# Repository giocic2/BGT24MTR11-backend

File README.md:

# BGT24MTR11-backend
KiCAD project of low frequency amplification and filtering stage

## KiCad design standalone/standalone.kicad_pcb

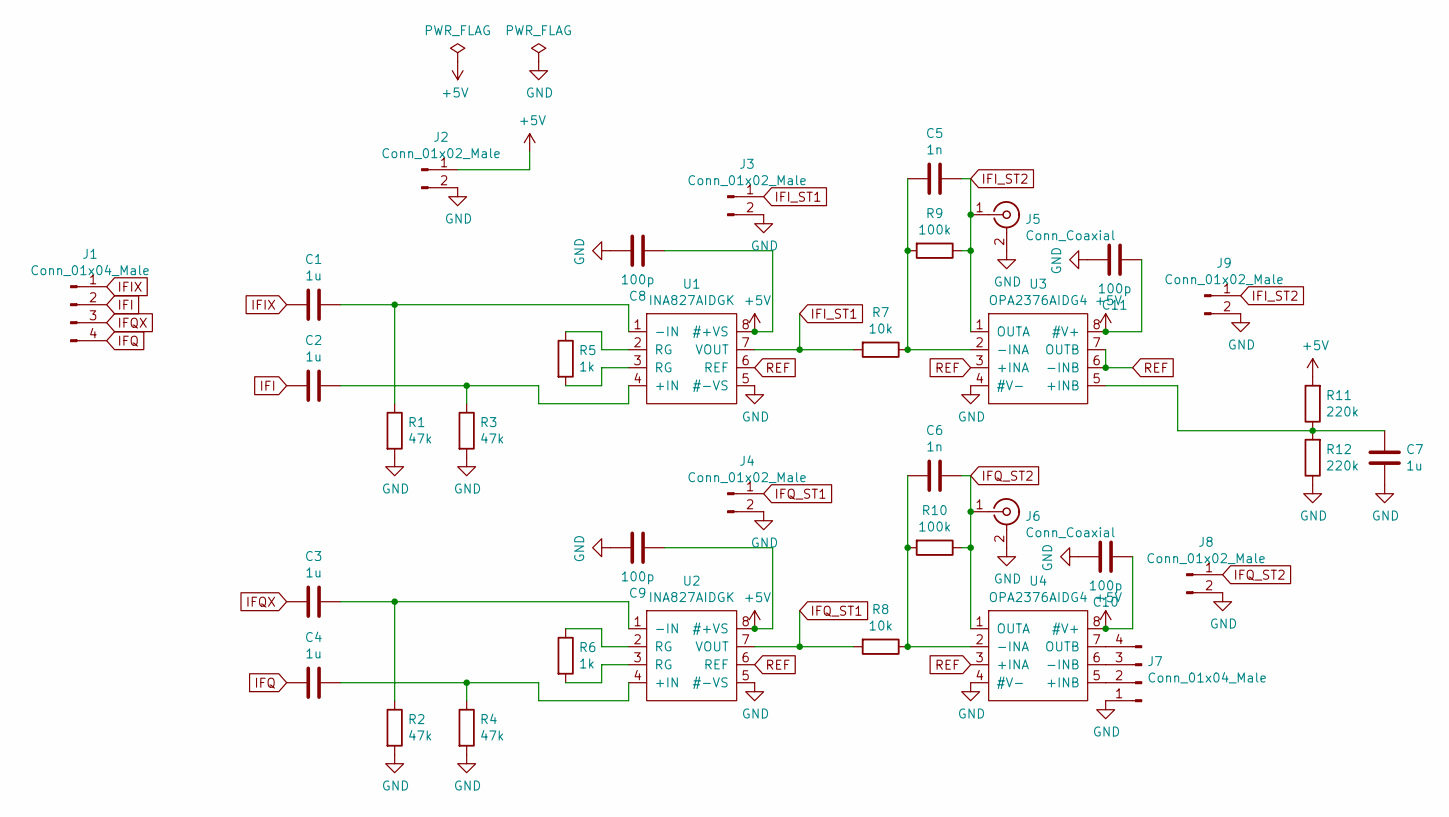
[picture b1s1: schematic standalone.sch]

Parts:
C1, C2, C3, C4, C7: 1u; C_0603_1608Metric_Pad1.08x0.95mm_HandSolder
C5, C6: 1n; C_0603_1608Metric_Pad1.08x0.95mm_HandSolder
C8, C9, C10, C11: 100p; C_0603_1608Metric_Pad1.08x0.95mm_HandSolder
J1, J7: Conn_01x04_Male; PinHeader_1x04_P2.54mm_Vertical
J2, J3, J4, J8, J9: Conn_01x02_Male; PinHeader_1x02_P2.54mm_Vertical
J5, J6: Conn_Coaxial; BNC_Amphenol_B6252HB-NPP3G-50_Horizontal
R1, R2, R3, R4: 47k; R_0603_1608Metric_Pad0.98x0.95mm_HandSolder
R5, R6: 1k; R_0603_1608Metric_Pad0.98x0.95mm_HandSolder
R7, R8: 10k; R_0603_1608Metric_Pad0.98x0.95mm_HandSolder
R9, R10: 100k; R_0603_1608Metric_Pad0.98x0.95mm_HandSolder
R11, R12: 220k; R_0603_1608Metric_Pad0.98x0.95mm_HandSolder
U1, U2: INA827AIDGK; VSSOP-8_3.0x3.0mm_P0.65mm
U3, U4: OPA2376AIDG4; SOIC-8_3.9x4.9mm_P1.27mm

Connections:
+5V: C8.2, C9.2, C10.2, C11.2, J2.1, R11.2, U1.8 (#+VS), U2.8 (#+VS), U3.8 (#V+), U4.8 (#V+)
GND: C7.1, C8.1, C9.1, C10.1, C11.1, J2.2, J3.2, J4.2, J5.2 (Ext), J6.2 (Ext), J7.1, J8.2, J9.2, R1.2, R2.2, R3.2, R4.2, R12.1, U1.5 (#-VS), U2.5 (#-VS), U3.4 (#V-), U4.4 (#V-)
IFI: C2.2, J1.2
IFIX: C1.2, J1.1
IFI_ST1: J3.1, R7.2, U1.7 (VOUT)
IFI_ST2: C5.1, J5.1 (In), J9.1, R9.1, U3.1 (OUTA)
IFQ: C4.2, J1.4
IFQX: C3.2, J1.3
IFQ_ST1: J4.1, R8.2, U2.7 (VOUT)
IFQ_ST2: C6.1, J6.1 (In), J8.1, R10.1, U4.1 (OUTA)
unnamed: C1.1, R1.1, U1.1 (-IN)
unnamed: C2.1, R3.1, U1.4 (+IN)
unnamed: C3.1, R2.1, U2.1 (-IN)
unnamed: C4.1, R4.1, U2.4 (+IN)
unnamed: C5.2, R7.1, R9.2, U3.2 (-INA)
unnamed: C6.2, R8.1, R10.2, U4.2 (-INA)
unnamed: C7.2, R11.1, R12.2, U3.5 (+INB)
unnamed: J7.2, U4.5 (+INB)
unnamed: J7.3, U4.6 (-INB)
unnamed: J7.4, U4.7 (OUTB)
unnamed: R5.1, U1.2 (RG)
unnamed: R5.2, U1.3 (RG)
unnamed: R6.1, U2.2 (RG)
unnamed: R6.2, U2.3 (RG)
REF: U1.6 (REF), U2.6 (REF), U3.3 (+INA), U3.6 (-INB), U3.7 (OUTB), U4.3 (+INA)

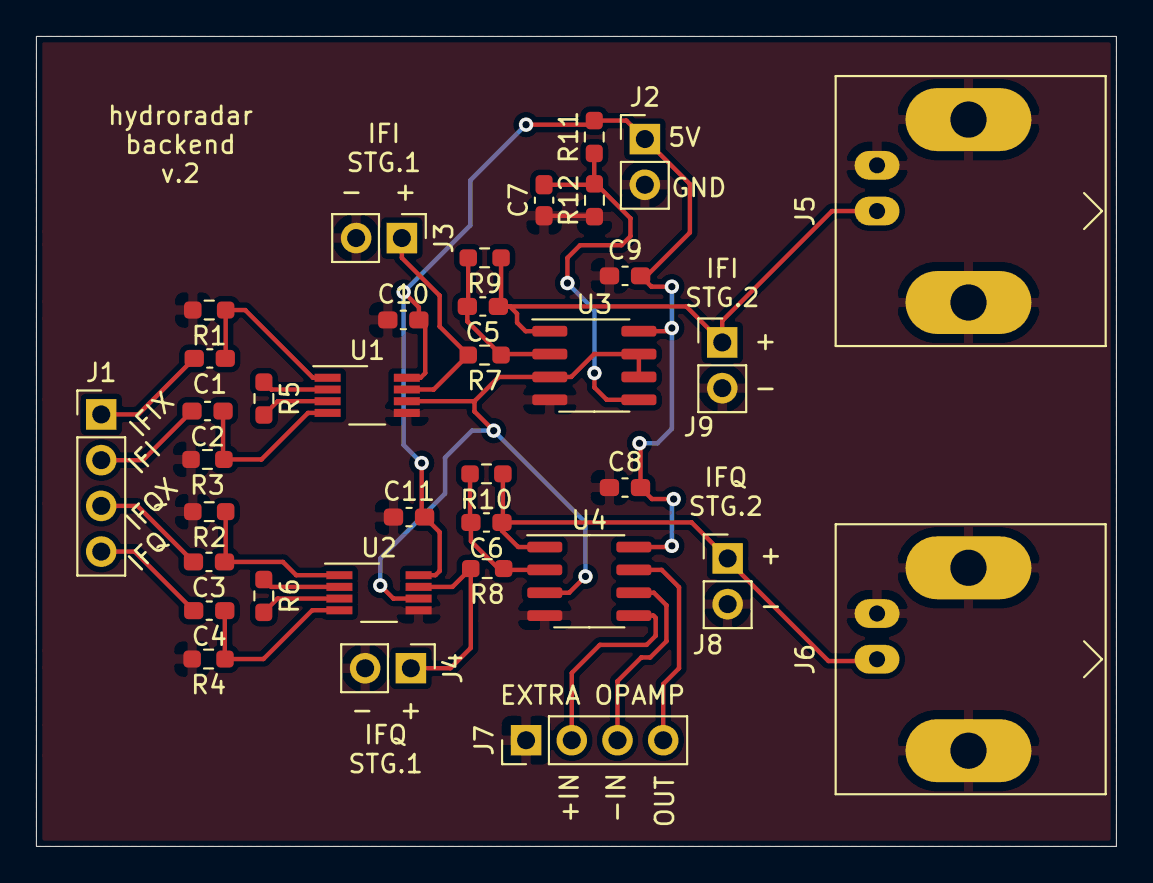
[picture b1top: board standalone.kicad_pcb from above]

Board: 2 copper layers, 60.0 x 45.0 mm, 36 parts (0 on the bottom side), 25 nets.

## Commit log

2021-12-02 symbols of INA and OPA created
2021-12-02 TI TINA material: SPICE simulations
2021-12-02 OPA2376 instead of OPA2137
2021-12-06 update TINA material
2021-12-09 schematic completed
2021-12-10 layout completed
2021-12-10 gerbers generated
2022-11-17 new schematic
2023-02-06 new: fmcw backend
2023-02-07 update: fmcw backend
